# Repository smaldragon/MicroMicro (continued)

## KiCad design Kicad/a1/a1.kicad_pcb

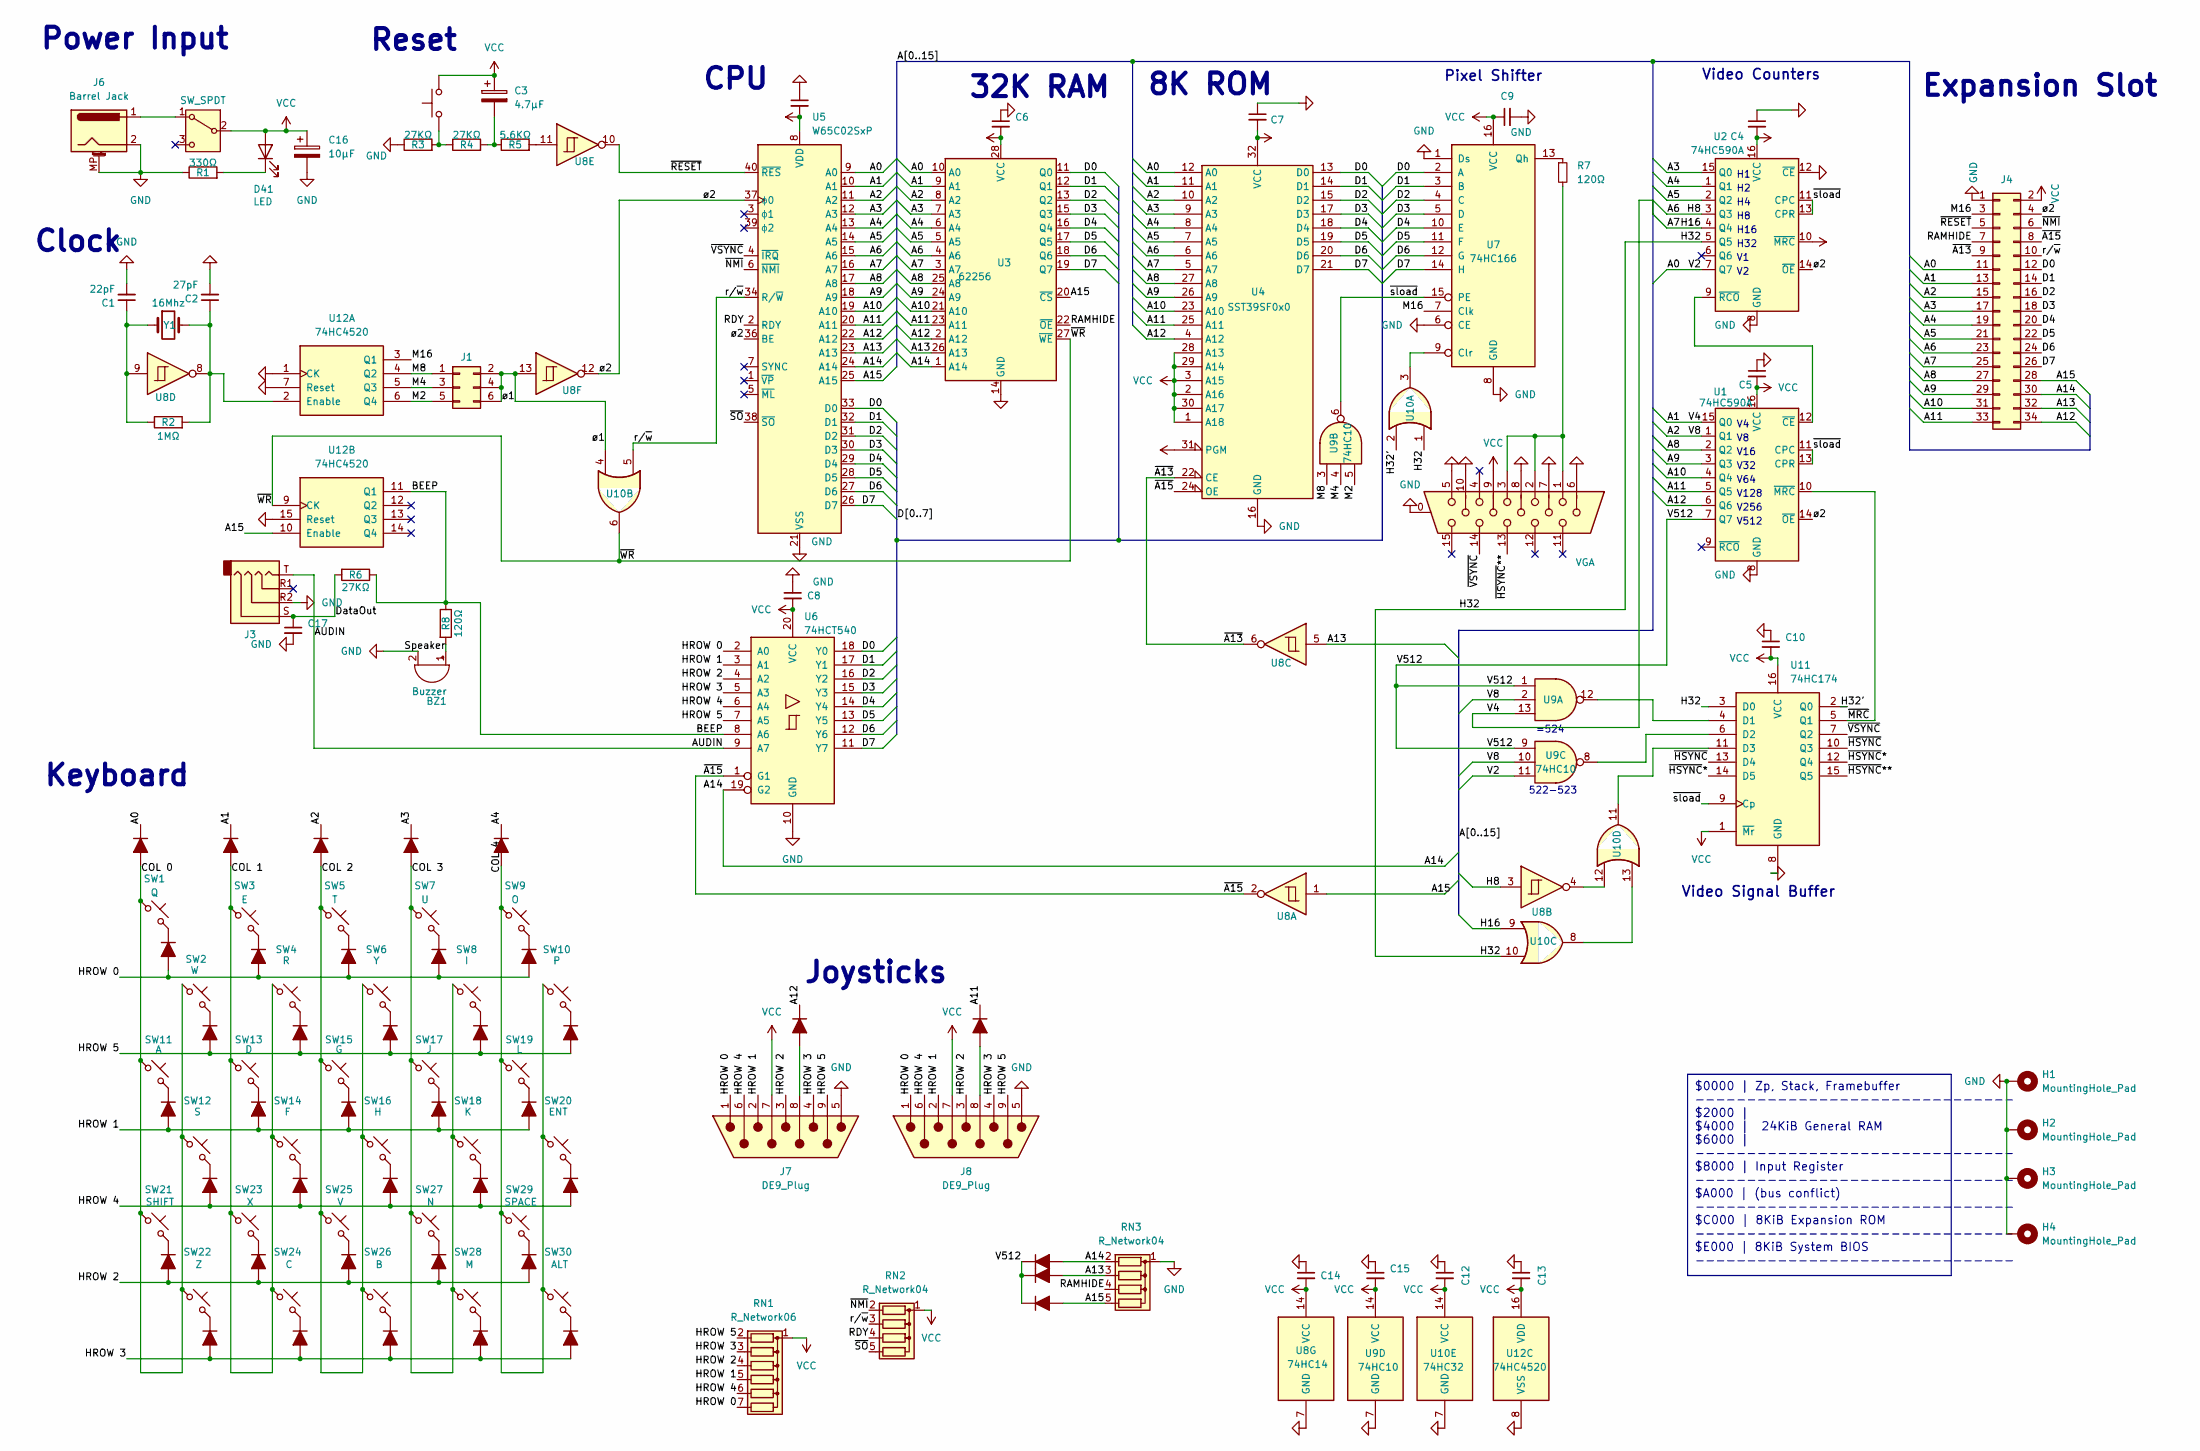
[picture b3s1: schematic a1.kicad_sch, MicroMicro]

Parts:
BZ1: Buzzer; MagneticBuzzer_Kingstate_KCG0601
C1: 22pF; C_Disc_D3.0mm_W1.6mm_P2.50mm
C2: 27pF; C_Disc_D3.0mm_W1.6mm_P2.50mm
C3: 4.7µF; CP_Radial_D4.0mm_P1.50mm
C4, C5, C6, C7, C8, C9, C10, C11, C12, C13, C14, C15, C17: 100nF; C_Disc_D3.0mm_W1.6mm_P2.50mm
C16: 10µF; CP_Radial_D5.0mm_P2.00mm
D1, D5, D6, D7, D8, D9, D10, D11, D12, D13, D14, D15, D16, D17, D18, D19, D20, D21, D22, D23, D24, D25, D26, D27, D28, D29, D30, D31, D32, D33, D34, D35, D36, D37, D38, D39, D40: 1N4148; D_DO-35_SOD27_P7.62mm_Horizontal
D2, D3, D4: 1N4148; D_DO-34_SOD68_P2.54mm_Vertical_KathodeUp
D41: LED; LED_Indicator_D3.0mm_W4.6mm_L6.5mm
H1, H2, H3, H4: MountingHole_Pad; MountingHole_2.2mm_M2_ISO7380_Pad
J1: Conn_02x03_Odd_Even; PinHeader_2x03_P2.54mm_Vertical
J2: VGA; DSUB-15-HD_Female_Horizontal_P2.29x1.98mm_EdgePinOffset3.03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
J3: AudioJack4; Jack_3.5mm_PJ320A_Horizontal
J4: Conn_02x17_Odd_Even; IDC-Header_2x17_P2.54mm_Horizontal
J6: Barrel Jack; BarrelJack_GCT_DCJ200-10-A_Horizontal
J7, J8: DE9_Plug; DSUB9-Atari
R1: 330Ω; R_Axial_DIN0204_L3.6mm_D1.6mm_P7.62mm_Horizontal
R2: 1MΩ; R_Axial_DIN0204_L3.6mm_D1.6mm_P7.62mm_Horizontal
R3, R4, R6: 27KΩ; R_Axial_DIN0204_L3.6mm_D1.6mm_P7.62mm_Horizontal
R5: 5.6KΩ; R_Axial_DIN0204_L3.6mm_D1.6mm_P7.62mm_Horizontal
R7, R8: 120Ω; R_Axial_DIN0204_L3.6mm_D1.6mm_P7.62mm_Horizontal
RN1: R_Network06; R_Array_SIP7
RN2, RN3: R_Network04; R_Array_SIP5
SW1: Q; SW_Redragon_MX_LowProfile_PCB_1.00u_Other
SW2: W; SW_Redragon_MX_LowProfile_PCB_1.00u_Other
SW3: E; SW_Redragon_MX_LowProfile_PCB_1.00u_Other
SW4: R; SW_Redragon_MX_LowProfile_PCB_1.00u_Other
SW5: T; SW_Redragon_MX_LowProfile_PCB_1.00u_Other
SW6: Y; SW_Redragon_MX_LowProfile_PCB_1.00u_Other
SW7: U; SW_Redragon_MX_LowProfile_PCB_1.00u_Other
SW8: I; SW_Redragon_MX_LowProfile_PCB_1.00u_Other
SW9: O; SW_Redragon_MX_LowProfile_PCB_1.00u_Other
SW10: P; SW_Redragon_MX_LowProfile_PCB_1.00u_Other
SW11: A; SW_Redragon_MX_LowProfile_PCB_1.00u_Other
SW12: S; SW_Redragon_MX_LowProfile_PCB_1.00u_Other
SW13: D; SW_Redragon_MX_LowProfile_PCB_1.00u_Other
SW14: F; SW_Redragon_MX_LowProfile_PCB_1.00u_Other
SW15: G; SW_Redragon_MX_LowProfile_PCB_1.00u_Other
SW16: H; SW_Redragon_MX_LowProfile_PCB_1.00u_Other
SW17: J; SW_Redragon_MX_LowProfile_PCB_1.00u_Other
SW18: K; SW_Redragon_MX_LowProfile_PCB_1.00u_Other
SW19: L; SW_Redragon_MX_LowProfile_PCB_1.00u_Other
SW20: ENT; SW_Redragon_MX_LowProfile_PCB_1.00u_Other
SW21: SHIFT; SW_Redragon_MX_LowProfile_PCB_1.00u_Other
SW22: Z; SW_Redragon_MX_LowProfile_PCB_1.00u_Other
SW23: X; SW_Redragon_MX_LowProfile_PCB_1.00u_Other
SW24: C; SW_Redragon_MX_LowProfile_PCB_1.00u_Other
SW25: V; SW_Redragon_MX_LowProfile_PCB_1.00u_Other
SW26: B; SW_Redragon_MX_LowProfile_PCB_1.00u_Other
SW27: N; SW_Redragon_MX_LowProfile_PCB_1.00u_Other
SW28: M; SW_Redragon_MX_LowProfile_PCB_1.00u_Other
SW29: SPACE; SW_Redragon_MX_LowProfile_PCB_1.00u_Other
SW30: ALT; SW_Redragon_MX_LowProfile_PCB_1.00u_Other
SW31: SW_Push; SW_Tactile_SKHH_Angled
SW32: SW_SPDT; SW_Slide_SPDT_Angled_CK_OS102011MA1Q
U1, U2: 74HC590A; DIP-16_W7.62mm_LongPads
U3: 62256; DIP-28_W15.24mm_LongPads
U4: SST39SF0x0; DIP-32_W15.24mm_LongPads
U5: W65C02SxP; DIP-40_W15.24mm
U6: 74HCT540; DIP-20_W7.62mm_LongPads
U7: 74HC166; DIP-16_W7.62mm_LongPads
U8: 74HC14; DIP-14_W7.62mm_LongPads
U9: 74HC10; DIP-14_W7.62mm_LongPads
U10: 74HC32; DIP-14_W7.62mm_LongPads
U11: 74HC174; DIP-16_W7.62mm_LongPads
U12: 74HC4520; DIP-16_W7.62mm_LongPads
Y1: 16Mhz; Crystal_HC49-4H_Vertical

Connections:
/A0: D1.1 (K), J4.11, U2.7 (Q7), U3.10 (A0), U4.12 (A0), U5.9 (A0), U9.11
/A1: D38.1 (K), J4.13, U1.15 (Q0), U3.9 (A1), U4.11 (A1), U5.10 (A1), U9.13
/A2: D39.1 (K), J4.15, U1.1 (Q1), U3.8 (A2), U4.10 (A2), U5.11 (A2), U9.2, U9.10
/A3: D40.1 (K), J4.17, U2.15 (Q0), U3.7 (A3), U4.9 (A3), U5.12 (A3)
/A4: D37.1 (K), J4.19, U2.1 (Q1), U3.6 (A4), U4.8 (A4), U5.13 (A4)
/A5: J4.21, U2.2 (Q2), U3.5 (A5), U4.7 (A5), U5.14 (A5)
/A6: J4.23, U2.3 (Q3), U3.4 (A6), U4.6 (A6), U5.15 (A6), U8.3
/A7: J4.25, U2.4 (Q4), U3.3 (A7), U4.5 (A7), U5.16 (A7), U10.9
/A8: J4.27, U1.2 (Q2), U3.25 (A8), U4.27 (A8), U5.17 (A8)
/A9: J4.29, U1.3 (Q3), U3.24 (A9), U4.26 (A9), U5.18 (A9)
/A10: J4.31, U1.4 (Q4), U3.21 (A10), U4.23 (A10), U5.19 (A10)
/A11: D5.1 (K), J4.33, U1.5 (Q5), U3.23 (A11), U4.25 (A11), U5.20 (A11)
/A12: D6.1 (K), J4.34, U1.6 (Q6), U3.2 (A12), U4.4 (A12), U5.22 (A12)
/A13: D3.2 (A), J4.32, RN3.3 (R2), U3.26 (A13), U5.23 (A13), U8.5
/A14: D2.2 (A), J4.30, RN3.2 (R1), U3.1 (A14), U5.24 (A14), U6.19 (G2)
/A15: D4.2 (A), J4.28, RN3.5 (R4), U3.20 (~CS), U5.25 (A15), U8.1, U12.10 (Enable)
/AUDIN: J3.T, U6.9 (A7)
/BEEP: R6.1, R8.1, U6.8 (A6), U12.11 (Q1)
/COL 0: D1.2 (A), SW1.1, SW2.1, SW11.1, SW12.1, SW21.1, SW22.1
/COL 1: D38.2 (A), SW3.1, SW4.1, SW13.1, SW14.1, SW23.1, SW24.1
/COL 2: D39.2 (A), SW5.1, SW6.1, SW15.1, SW16.1, SW25.1, SW26.1
/COL 3: D40.2 (A), SW7.1, SW8.1, SW17.1, SW18.1, SW27.1, SW28.1
/COL 4: D37.2 (A), SW9.1, SW10.1, SW19.1, SW20.1, SW29.1, SW30.1
/D0: J4.12, U3.11 (Q0), U4.13 (D0), U5.33 (D0), U6.18 (Y0), U7.2 (A)
/D1: J4.14, U3.12 (Q1), U4.14 (D1), U5.32 (D1), U6.17 (Y1), U7.3 (B)
/D2: J4.16, U3.13 (Q2), U4.15 (D2), U5.31 (D2), U6.16 (Y2), U7.4 (C)
/D3: J4.18, U3.15 (Q3), U4.17 (D3), U5.30 (D3), U6.15 (Y3), U7.5 (D)
/D4: J4.20, U3.16 (Q4), U4.18 (D4), U5.29 (D4), U6.14 (Y4), U7.10 (E)
/D5: J4.22, U3.17 (Q5), U4.19 (D5), U5.28 (D5), U6.13 (Y5), U7.11 (F)
/D6: J4.24, U3.18 (Q6), U4.20 (D6), U5.27 (D6), U6.12 (Y6), U7.12 (G)
/D7: J4.26, U3.19 (Q7), U4.21 (D7), U5.26 (D7), U6.11 (Y7), U7.14 (H)
/DataOut: C17.1, J3.S, R6.2
/H32: U2.5 (Q5), U10.1, U10.10, U11.3 (D0)
/H32': U10.2, U11.2 (Q0)
/HROW 0: D7.2 (A), D8.2 (A), D9.2 (A), D10.2 (A), D11.2 (A), J7.1, J8.1, RN1.7 (R6), U6.2 (A0)
/HROW 1: D17.2 (A), D18.2 (A), D19.2 (A), D20.2 (A), D21.2 (A), J7.2, J8.2, RN1.5 (R4), U6.3 (A1)
/HROW 2: D27.2 (A), D28.2 (A), D29.2 (A), D30.2 (A), D31.2 (A), J7.3, J8.3, RN1.4 (R3), U6.4 (A2)
/HROW 3: D32.2 (A), D33.2 (A), D34.2 (A), D35.2 (A), D36.2 (A), J7.4, J8.4, RN1.3 (R2), U6.5 (A3)
/HROW 4: D22.2 (A), D23.2 (A), D24.2 (A), D25.2 (A), D26.2 (A), J7.6, J8.6, RN1.6 (R5), U6.6 (A4)
/HROW 5: D12.2 (A), D13.2 (A), D14.2 (A), D15.2 (A), D16.2 (A), J7.9, J8.9, RN1.2 (R1), U6.7 (A5)
/M2: J1.5, U9.5, U12.6 (Q4)
/M4: J1.3, U9.4, U12.5 (Q3)
/M8: J1.1, U9.3, U12.4 (Q2)
/M16: J4.3, U7.7 (Clk), U12.3 (Q1)
/RAMHIDE: J4.7, RN3.4 (R3), U3.22 (~OE)
/RDY: RN2.4 (R3), U5.2 (RDY)
/Speaker: BZ1.1 (+), R8.2
/V512: D2.1 (K), D3.1 (K), D4.1 (K), U1.7 (Q7), U9.1, U9.9
/r/~w: J4.10, RN2.3 (R2), U5.34 (R/~W), U10.5
/~A13: J4.9, U4.22 (CE), U8.6
/~A15: J4.8, U4.24 (OE), U6.1 (G1), U8.2
/~HSYNC: U11.10 (Q3), U11.13 (D4)
/~HSYNC*: U11.12 (Q4), U11.14 (D5)
/~HSYNC**: J2.13, U11.15 (Q5)
/~MRC: U1.10 (~MRC), U11.5 (Q1)
/~NMI: J4.6, RN2.2 (R1), U5.6 (~NMI)
/~RESET: J4.5, U5.40 (~RES), U8.10
/~SO: RN2.5 (R4), U5.38 (~SO)
/~VSYNC: J2.14, U5.4 (~IRQ), U11.7 (Q2)
/~WR: U3.27 (~WE), U10.6, U12.9 (CK)
/~sload: U1.11 (CPC), U1.13 (CPR), U2.11 (CPC), U2.13 (CPR), U7.15 (PE), U9.6, U11.9 (Cp)
/ø1: J1.2, J1.4, J1.6, U8.13, U10.4
/ø2: J4.4, U1.14 (~OE), U2.14 (~OE), U5.36 (BE), U5.37 (ϕ0), U8.12
GND: BZ1.2 (-), C1.2, C2.2, C4.1, C5.1, C6.1, C7.1, C8.1, C9.2, C10.1, C11.1, C12.1, C13.1, C14.1, C15.1, C16.2, C17.2, H1.1, H2.1, H3.1, H4.1, J2.0, J2.5, J2.6, J2.7, J2.8, J2.10, J3.R2, J4.1, J6.2, J6.MP (MountPin), J7.5, J8.5, R1.1, R3.1, RN3.1 (common), U1.8 (GND), U2.8 (GND), U2.12 (~CE), U3.14 (GND), U4.16 (GND), U5.21 (VSS), U6.10 (GND), U7.1 (Ds), U7.6 (CE), U7.8 (GND), U8.7 (GND), U9.7 (GND), U10.7 (GND), U11.8 (GND), U12.1 (CK), U12.7 (Reset), U12.8 (VSS), U12.15 (Reset)
unnamed: C1.1, R2.1, U8.9, Y1.1
unnamed: C3.2, R4.2, R5.1
unnamed: D5.2 (A), J8.8
unnamed: D6.2 (A), J7.8
unnamed: D7.1 (K), SW1.2
unnamed: D8.1 (K), SW3.2
unnamed: D9.1 (K), SW5.2
unnamed: D10.1 (K), SW7.2
unnamed: D11.1 (K), SW9.2
unnamed: D12.1 (K), SW10.2
unnamed: D13.1 (K), SW8.2
unnamed: D14.1 (K), SW6.2
unnamed: D15.1 (K), SW4.2
unnamed: D16.1 (K), SW2.2
unnamed: D17.1 (K), SW11.2
unnamed: D18.1 (K), SW13.2
unnamed: D19.1 (K), SW15.2
unnamed: D20.1 (K), SW17.2
unnamed: D21.1 (K), SW19.2
unnamed: D22.1 (K), SW12.2
unnamed: D23.1 (K), SW14.2
unnamed: D24.1 (K), SW16.2
unnamed: D25.1 (K), SW18.2
unnamed: D26.1 (K), SW20.2
unnamed: D27.1 (K), SW21.2
unnamed: D28.1 (K), SW23.2
unnamed: D29.1 (K), SW25.2
unnamed: D30.1 (K), SW27.2
unnamed: D31.1 (K), SW29.2
unnamed: D32.1 (K), SW22.2
unnamed: D33.1 (K), SW24.2
unnamed: D34.1 (K), SW26.2
unnamed: D35.1 (K), SW28.2
unnamed: D36.1 (K), SW30.2
unnamed: D41.1 (K), R1.2
unnamed: J2.1, J2.2, J2.3, R7.2
unnamed: R3.2, R4.1, SW31.1
unnamed: R5.2, U8.11
unnamed: J6.1, SW32.1 (A)
unnamed: U1.12 (~CE), U2.9 (~RCO)
unnamed: U7.9 (Clr), U10.3
unnamed: R7.1, U7.13 (Qh)
unnamed: U8.4, U10.12
unnamed: U10.8, U10.13
unnamed: U9.12, U11.4 (D1)
unnamed: U9.8, U11.6 (D2)
unnamed: U10.11, U11.11 (D3)
unnamed: C2.1, R2.2, U8.8, U12.2 (Enable), Y1.2
VCC: C3.1, C4.2, C5.2, C6.2, C7.2, C8.2, C9.1, C10.2, C11.2, C12.2, C13.2, C14.2, C15.2, C16.1, D41.2 (A), J2.9, J4.2, J7.7, J8.7, RN1.1 (common), RN2.1 (common), SW31.2, SW32.2 (B), U1.16 (VCC), U2.10 (~MRC), U2.16 (VCC), U3.28 (VCC), U4.1 (A18), U4.2 (A16), U4.3 (A15), U4.28 (A13), U4.29 (A14), U4.30 (A17), U4.31 (PGM), U4.32 (VCC), U5.8 (VDD), U6.20 (VCC), U7.16 (VCC), U8.14 (VCC), U9.14 (VCC), U10.14 (VCC), U11.1 (~Mr), U11.16 (VCC), U12.16 (VDD)

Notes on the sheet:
$0000 | Zp, Stack, Framebuffer ------------------------------- $2000 | $4000 | 24KiB General RAM $6000 | ------------------------------- $8000 | Input Register ------------------------------- $A000 | (bus conflict) ------------------------------- $C000 | 8KiB Expansion ROM -------------------------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
Video Signal Buffer
Pixel Shifter
=524
H16
Expansion Slot
32K RAM
522-523
Keyboard
Power Input
CPU
V128
H32
Video Counters
V32
V64
Joysticks
V16
Clock
V512
V256
Reset
8K ROM

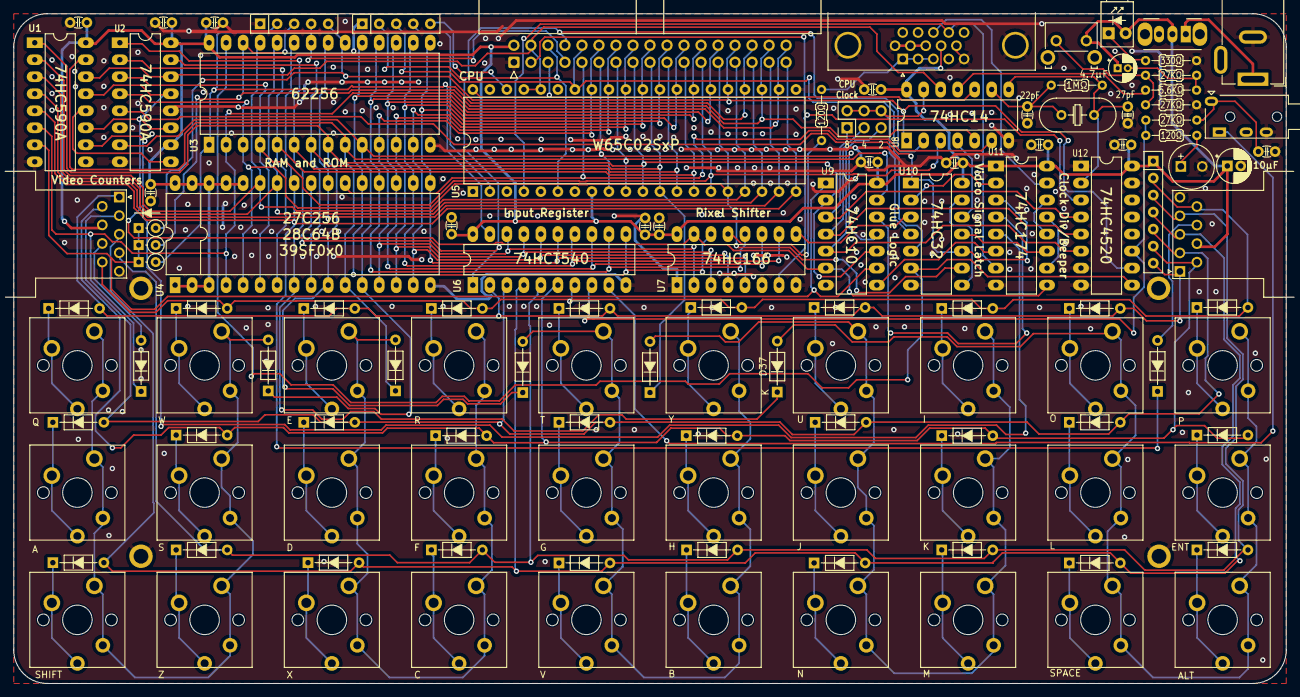
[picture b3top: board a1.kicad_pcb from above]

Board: 2 copper layers, 190.0 x 100.0 mm, 126 parts (0 on the bottom side), 113 nets.

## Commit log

2024-10-13 Update images
2024-11-14 add .gitignore
2024-11-14 add kicad, emulator, bios files
2024-11-15 add sound emulation
2024-11-25 pcb,bios,font improvements
2024-11-27 update pcb
2024-12-16 update system logic
2024-12-16 file update
2025-01-08 Update pcb and readme
2025-01-08 update render image
2025-01-16 tweak pcb, change key layout
2025-01-19 Silkscreen tweaks
2025-01-23 Emulator and Bios Improvements
2025-01-31 Updated PCBs and Code
2025-02-06 tweak clock circuit
2025-02-06 fix PJ-320A (headphone jack) footprint
2025-02-10 file rename command
2025-03-21 OS Command Improvements * PEEK can now read X number of bytes * POKE added * PRUN added * README updated
2025-04-01 Circuit Tweaks
2025-04-05 add 2 more m2 screw posts
2025-04-06 Big a2 update
2025-04-10 Specify MCP100 H boundout version (why are there 2)
2025-04-10 tweak resitor values
2025-04-11 fix bios bug, update readme
2025-04-11 improve emulation, bios input
2025-05-28 Various tweaks * Add "Docs" folder * Add "BEEP" function to BIOS * Add Function table to BIOS
2025-05-31 extra command table test!
2025-07-05 Finally add window resizing
2025-07-05 add html bom
2025-07-05 Add interactive BOM link to README
2025-11-23 add banked expansion roms to the emulator
2025-11-24 a3 board
2025-12-02 Add wasm build :)
2025-12-11 switch to SDL_QueueAudio
2025-12-14 Add missing wdc65c02 instructions (untested)
2025-12-15 switch cpu to submodule
2025-12-17 More Bios Documentation, More Bios Functionality
2025-12-17 actually use the labels in TestCMD :)
2026-01-04 docs readibility tweak
2026-01-05 Scrolling Routine Changes
2026-01-05 fix unitialized activefooter variable
2026-01-05 SETCURSOR/GETCURSOR, FOOTER and Bugfixes
2026-01-05 GETCURSOR/SETCURSOR, Footer and Bugfixes
2026-01-12 Add TTL/MIC level jumper to trs jack
